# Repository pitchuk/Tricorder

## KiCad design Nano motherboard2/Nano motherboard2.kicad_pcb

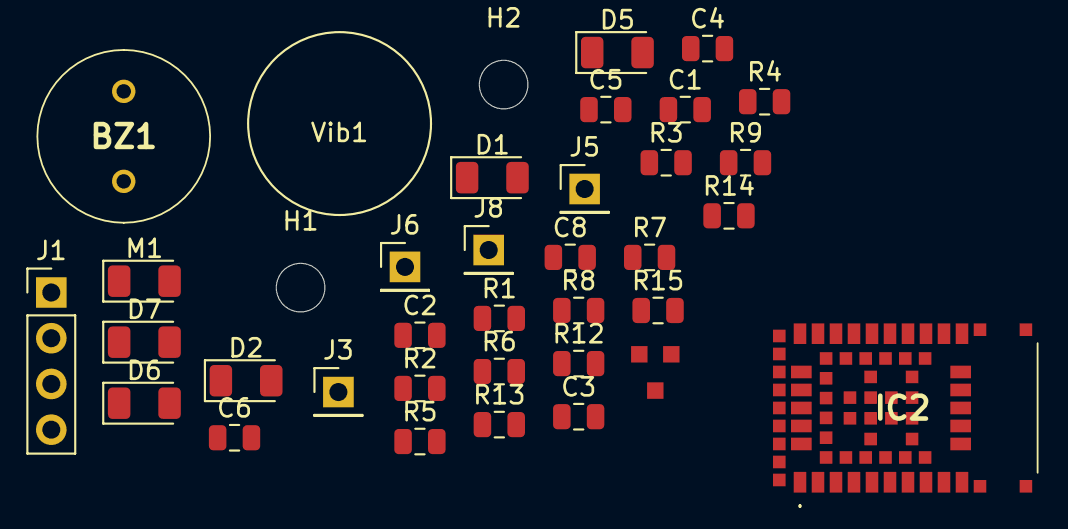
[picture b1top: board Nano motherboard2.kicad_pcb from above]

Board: 2 copper layers, 37 parts (0 on the bottom side), 11 nets, no tracks yet.

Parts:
BZ1: Buzzer; CMI9605IC0380T
C1, C8: C; C_0805_2012Metric
C2: 10uF; C_0805_2012Metric
C3: 4.7uF; C_0805_2012Metric
C4: 100nF; C_0805_2012Metric
C5: 10 pF; C_0805_2012Metric
C6: 0.1uF; C_0805_2012Metric
D1, D2, D7: D; D_1206_3216Metric
D5, D6: 1N4148; D_1206_3216Metric
H1, H2: MountingHole; MountingHole_2.7mm_M2.5
IC2: NINA-B306-00B; NINAB30600B
J1: I2C_Sceen; PinHeader_1x04_P2.54mm_Vertical
J3, J5: Batt_Term_VCC; PinHeader_1x01_P2.54mm_Vertical
J6, J8: Batt_Term_GND; PinHeader_1x01_P2.54mm_Vertical
M1: Vibration_Motor_DC; D_1206_3216Metric
Q4: Q_NPN_BCE; SOT23-3
R1, R5, R9: 10k; R_0805_2012Metric
R2: 3K5; R_0805_2012Metric
R3, R4, R14, R15: R; R_0805_2012Metric
R6, R7, R8: 100k; R_0805_2012Metric
R12, R13: 200; R_0805_2012Metric
Vib1: Vib_Disk

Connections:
3.3V: BZ1.1, C1.1, C2.2, C8.1, D1.1, D7.1, J1.3, M1.1, R2.2, R12.2, R13.1
5V_OUT: D2.1, J3.1, J5.1, R6.2, R7.1
Batt_Measure: R5.2, R9.1
GND: C2.1, C3.1, C4.1, C5.1, J1.4, J6.1, J8.1, Q4.3, R3.2, R9.2, R15.2
unnamed: BZ1.2, C8.2, D7.2, R14.1
unnamed: C1.2, D1.2, M1.2, R4.1
unnamed: C4.2, C5.2, D5.1, D6.1
unnamed: C6.1, R1.2
unnamed: Q4.2, R7.2
unnamed: D6.2, R12.1
unnamed: Q4.1, R8.2

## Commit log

2022-01-13 first upload
2022-01-13 value changes
2022-01-18 changes rtc etc
2022-01-18 More RTC and Screen changes
